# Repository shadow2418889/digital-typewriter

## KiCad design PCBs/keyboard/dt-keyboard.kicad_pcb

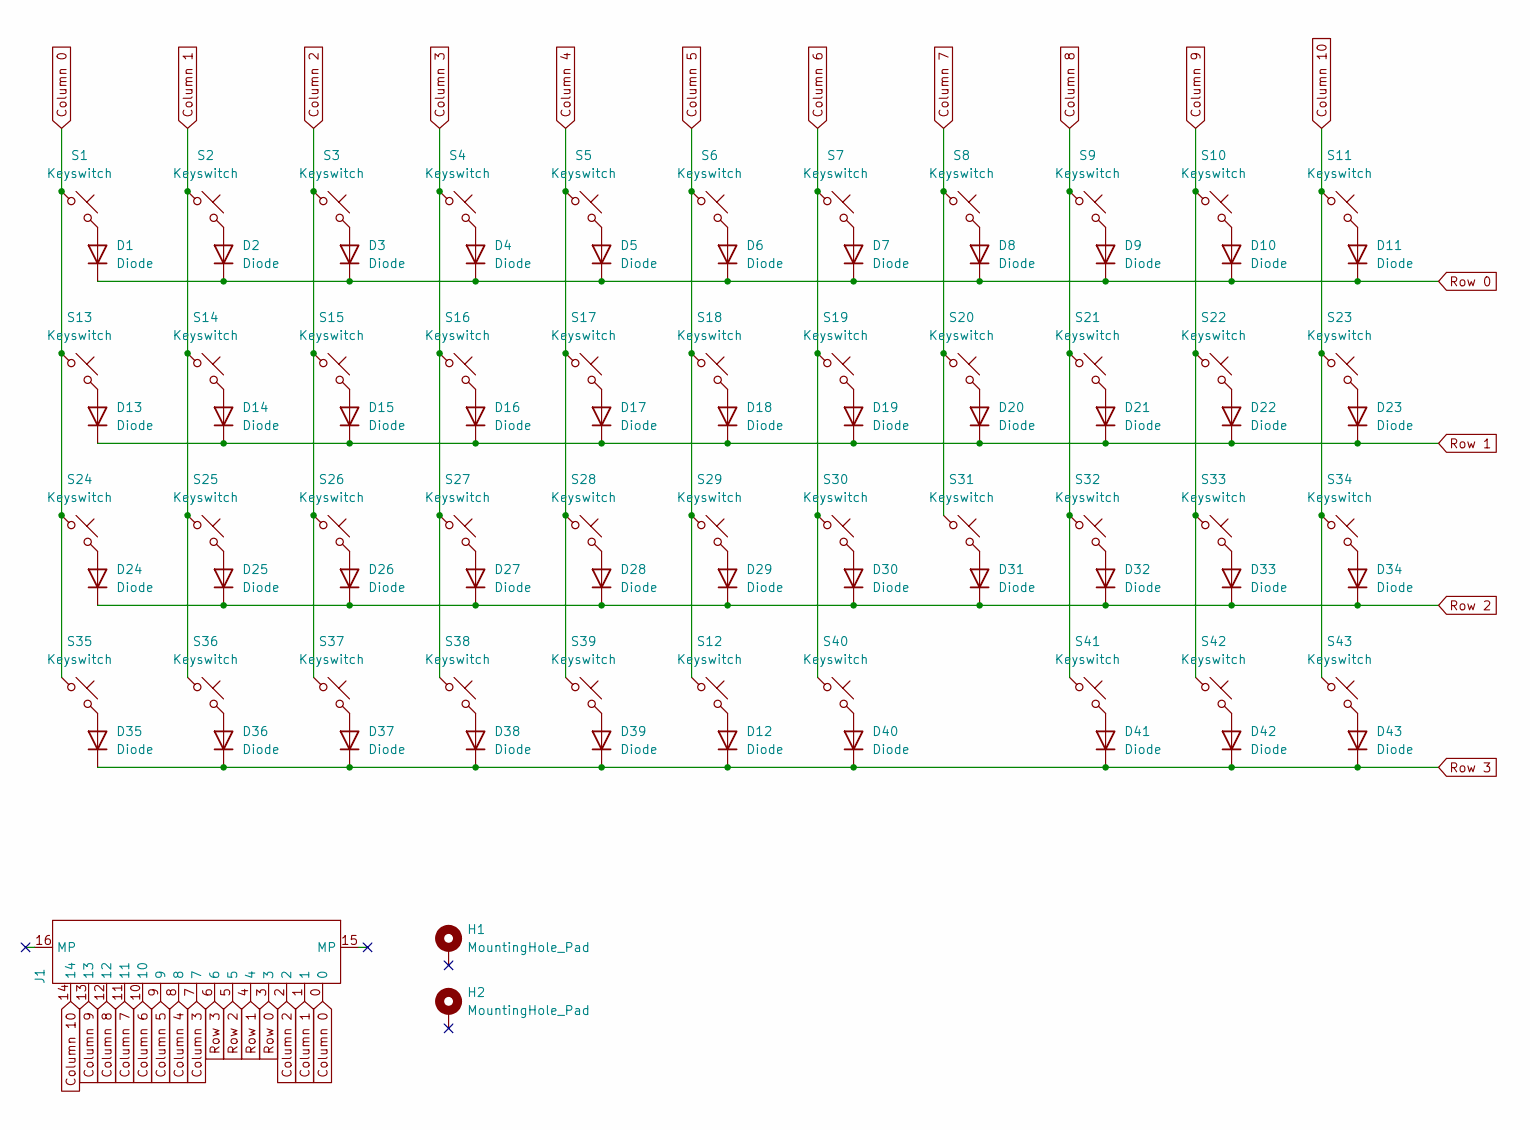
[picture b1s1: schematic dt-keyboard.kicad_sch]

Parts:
D1, D2, D3, D4, D5, D6, D7, D8, D9, D10, D11, D12, D13, D14, D15, D16, D17, D18, D19, D20, D21, D22, D23, D24, D25, D26, D27, D28, D29, D30, D31, D32, D33, D34, D35, D36, D37, D38, D39, D40, D41, D42, D43: Diode; Diode_SOD-123
H1, H2: MountingHole_Pad; MountingHole_3.2mm_M3_Pad_TopBottom
J1: FPC_15
S1, S2, S3, S4, S5, S6, S7, S8, S9, S10, S11, S12, S14, S15, S16, S17, S18, S19, S20, S21, S22, S25, S26, S27, S28, S29, S30, S31, S32, S34, S36, S37, S39, S41, S42: Keyswitch; MX Hotswap_Choc_V1_Plated_1.00u
S13, S33, S35, S43: Keyswitch; MX Hotswap_Choc_V1_Plated_1.25u
S23, S24: Keyswitch; MX Hotswap_Choc_V1_Plated_1.75u
S38, S40: Keyswitch; MX Hotswap_Choc_V1_Plated_2.25u

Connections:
Column 0: J1.0, S1.1, S13.1, S24.1, S35.1
Column 1: J1.1, S2.1, S14.1, S25.1, S36.1
Column 2: J1.2, S3.1, S15.1, S26.1, S37.1
Column 3: J1.7, S4.1, S16.1, S27.1, S38.1
Column 4: J1.8, S5.1, S17.1, S28.1, S39.1
Column 5: J1.9, S6.1, S12.1, S18.1, S29.1
Column 6: J1.10, S7.1, S19.1, S30.1, S40.1
Column 7: J1.11, S8.1, S20.1, S31.1
Column 8: J1.12, S9.1, S21.1, S32.1, S41.1
Column 9: J1.13, S10.1, S22.1, S33.1, S42.1
Column 10: J1.14, S11.1, S23.1, S34.1, S43.1
unnamed: D1.2 (A), S1.2
unnamed: D2.2 (A), S2.2
unnamed: D3.2 (A), S3.2
unnamed: D4.2 (A), S4.2
unnamed: D5.2 (A), S5.2
unnamed: D6.2 (A), S6.2
unnamed: D7.2 (A), S7.2
unnamed: D8.2 (A), S8.2
unnamed: D9.2 (A), S9.2
unnamed: D10.2 (A), S10.2
unnamed: D11.2 (A), S11.2
unnamed: D12.2 (A), S12.2
unnamed: D13.2 (A), S13.2
unnamed: D14.2 (A), S14.2
unnamed: D15.2 (A), S15.2
unnamed: D16.2 (A), S16.2
unnamed: D17.2 (A), S17.2
unnamed: D18.2 (A), S18.2
unnamed: D19.2 (A), S19.2
unnamed: D20.2 (A), S20.2
unnamed: D21.2 (A), S21.2
unnamed: D22.2 (A), S22.2
unnamed: D23.2 (A), S23.2
unnamed: D24.2 (A), S24.2
unnamed: D25.2 (A), S25.2
unnamed: D26.2 (A), S26.2
unnamed: D27.2 (A), S27.2
unnamed: D28.2 (A), S28.2
unnamed: D29.2 (A), S29.2
unnamed: D30.2 (A), S30.2
unnamed: D31.2 (A), S31.2
unnamed: D32.2 (A), S32.2
unnamed: D33.2 (A), S33.2
unnamed: D34.2 (A), S34.2
unnamed: D35.2 (A), S35.2
unnamed: D36.2 (A), S36.2
unnamed: D37.2 (A), S37.2
unnamed: D38.2 (A), S38.2
unnamed: D39.2 (A), S39.2
unnamed: D40.2 (A), S40.2
unnamed: D41.2 (A), S41.2
unnamed: D42.2 (A), S42.2
unnamed: D43.2 (A), S43.2
Row 0: D1.1 (K), D2.1 (K), D3.1 (K), D4.1 (K), D5.1 (K), D6.1 (K), D7.1 (K), D8.1 (K), D9.1 (K), D10.1 (K), D11.1 (K), J1.3
Row 1: D13.1 (K), D14.1 (K), D15.1 (K), D16.1 (K), D17.1 (K), D18.1 (K), D19.1 (K), D20.1 (K), D21.1 (K), D22.1 (K), D23.1 (K), J1.4
Row 2: D24.1 (K), D25.1 (K), D26.1 (K), D27.1 (K), D28.1 (K), D29.1 (K), D30.1 (K), D31.1 (K), D32.1 (K), D33.1 (K), D34.1 (K), J1.5
Row 3: D12.1 (K), D35.1 (K), D36.1 (K), D37.1 (K), D38.1 (K), D39.1 (K), D40.1 (K), D41.1 (K), D42.1 (K), D43.1 (K), J1.6

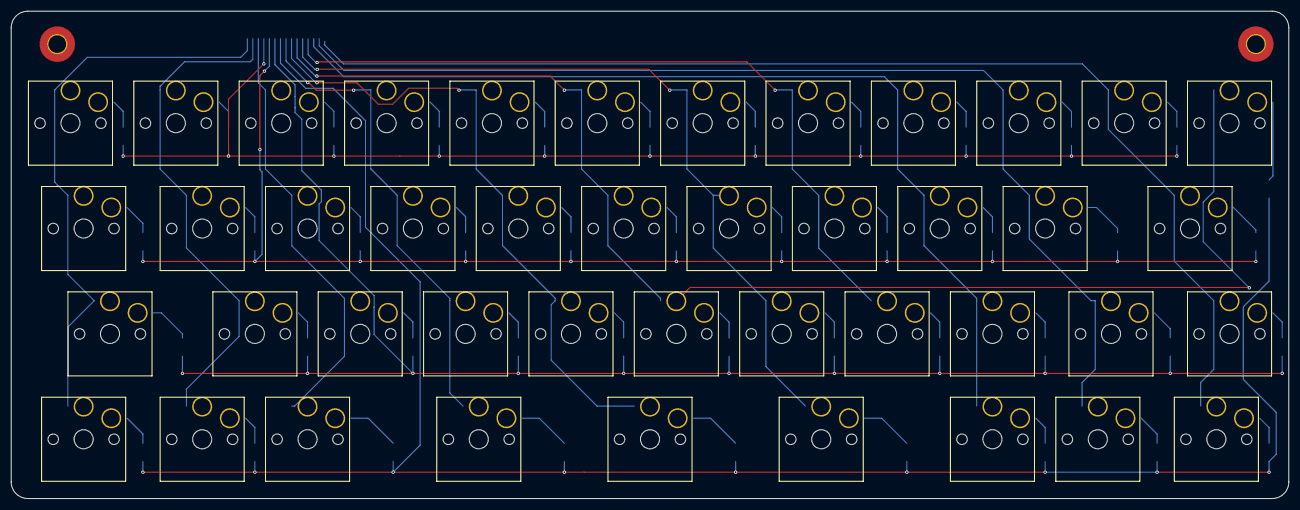
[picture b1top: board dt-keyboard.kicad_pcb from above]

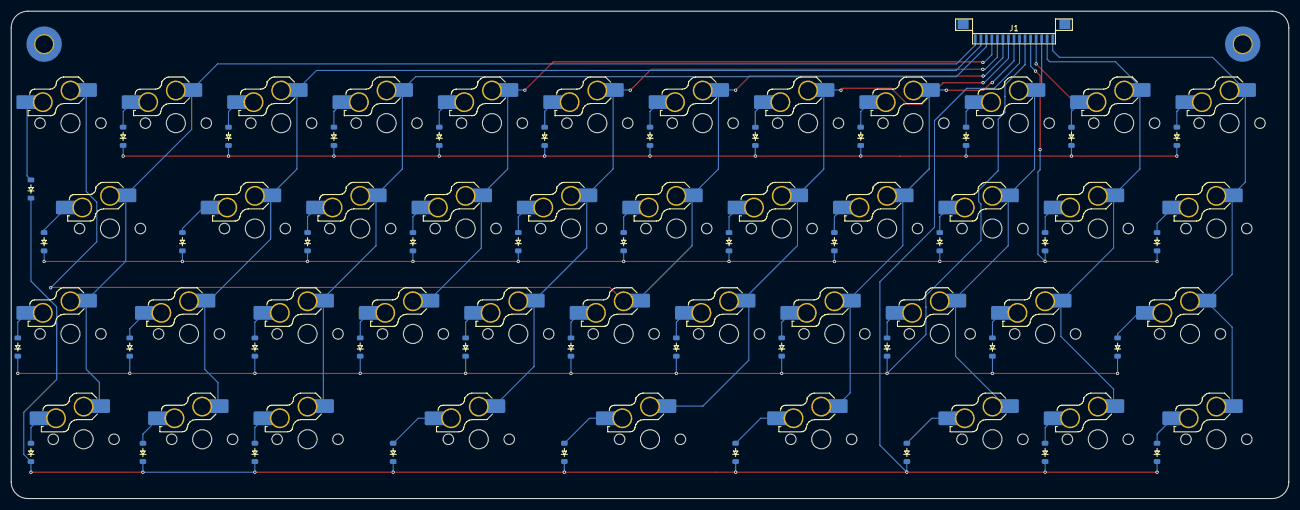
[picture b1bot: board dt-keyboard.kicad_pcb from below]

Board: 2 copper layers, 231.0 x 88.1 mm, 89 parts (44 on the bottom side), 58 nets.

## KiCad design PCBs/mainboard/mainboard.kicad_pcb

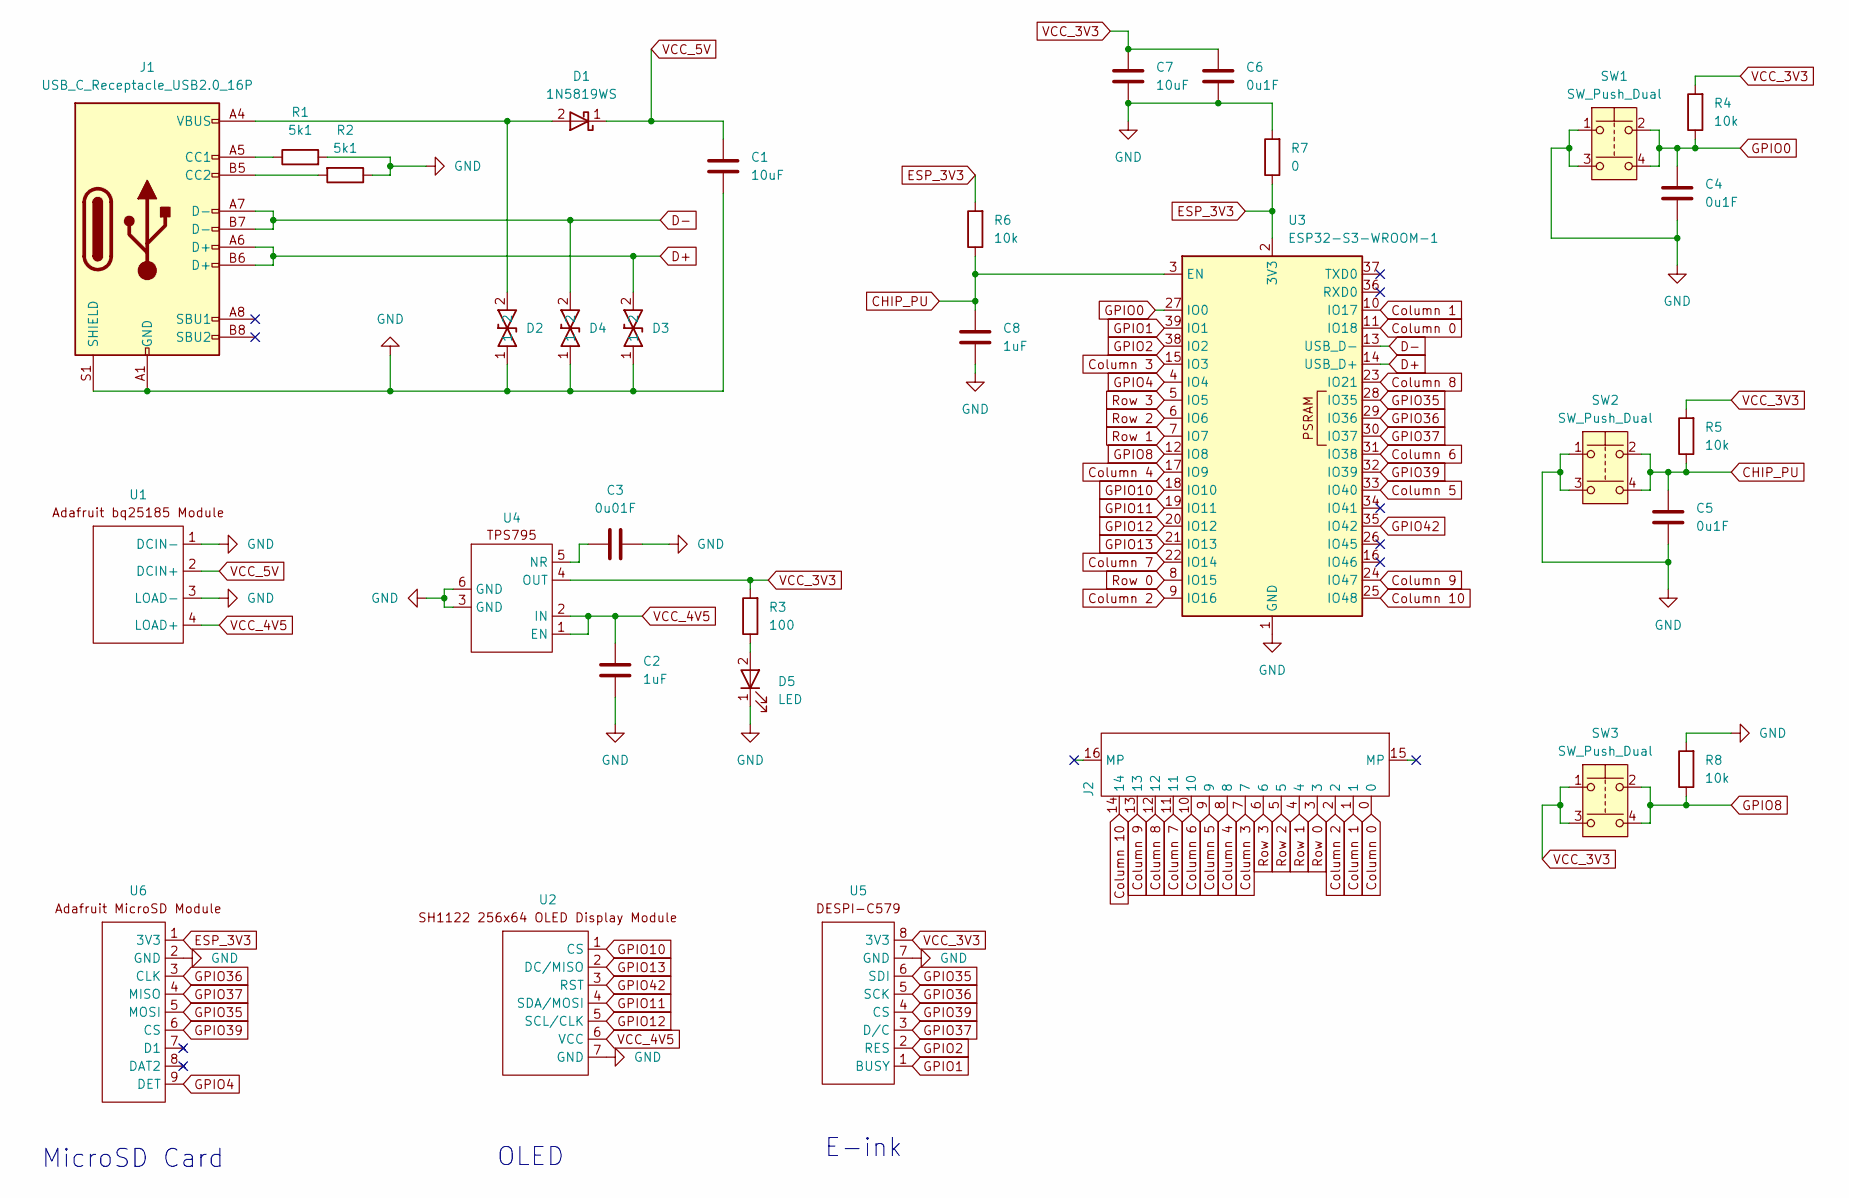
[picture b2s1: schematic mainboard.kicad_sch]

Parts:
C1, C7: 10uF; C_0805_2012Metric
C2, C8: 1uF; C_0805_2012Metric
C3: 0u01F; C_0805_2012Metric
C4, C5, C6: 0u1F; C_0805_2012Metric
D1: 1N5819WS; 1N5819HW-7-F
D2, D3, D4: LESD5D5
D5: LED; KT-0805G
J1: USB_C_Receptacle_USB2.0_16P; USB_C_Receptacle_16P
J2: FPC_15
R1, R2: 5k1; R_0805_2012Metric
R3: 100; R_0805_2012Metric
R4, R5, R6, R8: 10k; R_0805_2012Metric
R7: 0; R_0805_2012Metric
SW1, SW2, SW3: SW_Push_Dual; B3F-1000
U1: Adafruit bq25185 Module
U2: SH1122 256x64 OLED Display Module
U3: ESP32-S3-WROOM-1
U4: TPS795
U5: DESPI-C579
U6: Adafruit MicroSD Module

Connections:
CHIP_PU: C5.1, C8.1, R5.1, R6.1, SW2.2, SW2.4, U3.3 (EN)
Column 0: J2.0, U3.11 (IO18)
Column 1: J2.1, U3.10 (IO17)
Column 2: J2.2, U3.9 (IO16)
Column 3: J2.7, U3.15 (IO3)
Column 4: J2.8, U3.17 (IO9)
Column 5: J2.9, U3.33 (IO40)
Column 6: J2.10, U3.31 (IO38)
Column 7: J2.11, U3.22 (IO14)
Column 8: J2.12, U3.23 (IO21)
Column 9: J2.13, U3.24 (IO47)
Column 10: J2.14, U3.25 (IO48)
D+: D3.2, J1.A6 (D+), J1.B6 (D+), U3.14 (USB_D+)
D-: D4.2, J1.A7 (D-), J1.B7 (D-), U3.13 (USB_D-)
ESP_3V3: R6.2, R7.1, U3.2 (3V3), U6.1 (3V3)
GND: C1.2, C2.2, C3.1, C4.2, C5.2, C6.2, C7.2, C8.2, D2.1, D3.1, D4.1, D5.1 (K), J1.A1 (GND), J1.A12 (GND), J1.B1 (GND), J1.B12 (GND), J1.S1 (SHIELD), R1.2, R2.1, R7.2, R8.2, SW1.1, SW1.3, SW2.1, SW2.3, U1.1 (DCIN-), U1.3 (LOAD-), U2.7 (GND), U3.1 (GND), U3.40 (GND), U3.41 (GND), U4.3 (GND), U4.6 (GND), U5.7 (GND), U6.2 (GND)
GPIO0: C4.1, R4.1, SW1.2, SW1.4, U3.27 (IO0)
GPIO1: U3.39 (IO1), U5.1 (BUSY)
GPIO2: U3.38 (IO2), U5.2 (RES)
GPIO4: U3.4 (IO4), U6.9 (DET)
GPIO8: R8.1, SW3.2, SW3.4, U3.12 (IO8)
GPIO10: U2.1 (CS), U3.18 (IO10)
GPIO11: U2.4 (SDA/MOSI), U3.19 (IO11)
GPIO12: U2.5 (SCL/CLK), U3.20 (IO12)
GPIO13: U2.2 (DC/MISO), U3.21 (IO13)
GPIO35: U3.28 (IO35), U5.6 (SDI), U6.5 (MOSI)
GPIO36: U3.29 (IO36), U5.5 (SCK), U6.3 (CLK)
GPIO37: U3.30 (IO37), U5.3 (D/C), U6.4 (MISO)
GPIO39: U3.32 (IO39), U5.4 (CS), U6.6 (CS)
GPIO42: U2.3 (RST), U3.35 (IO42)
unnamed: D1.2 (A), D2.2, J1.A4 (VBUS), J1.A9 (VBUS), J1.B4 (VBUS), J1.B9 (VBUS)
unnamed: D5.2 (A), R3.1
unnamed: J1.A5 (CC1), R1.1
unnamed: J1.B5 (CC2), R2.2
unnamed: C3.2, U4.5 (NR)
Row 0: J2.3, U3.8 (IO15)
Row 1: J2.4, U3.7 (IO7)
Row 2: J2.5, U3.6 (IO6)
Row 3: J2.6, U3.5 (IO5)
VCC_3V3: C6.1, C7.1, R3.2, R4.2, R5.2, SW3.1, SW3.3, U4.4 (OUT), U5.8 (3V3)
VCC_4V5: C2.1, U1.4 (LOAD+), U2.6 (VCC), U4.1 (EN), U4.2 (IN)
VCC_5V: C1.1, D1.1 (K), U1.2 (DCIN+)

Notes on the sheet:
MicroSD Card
OLED
E-ink

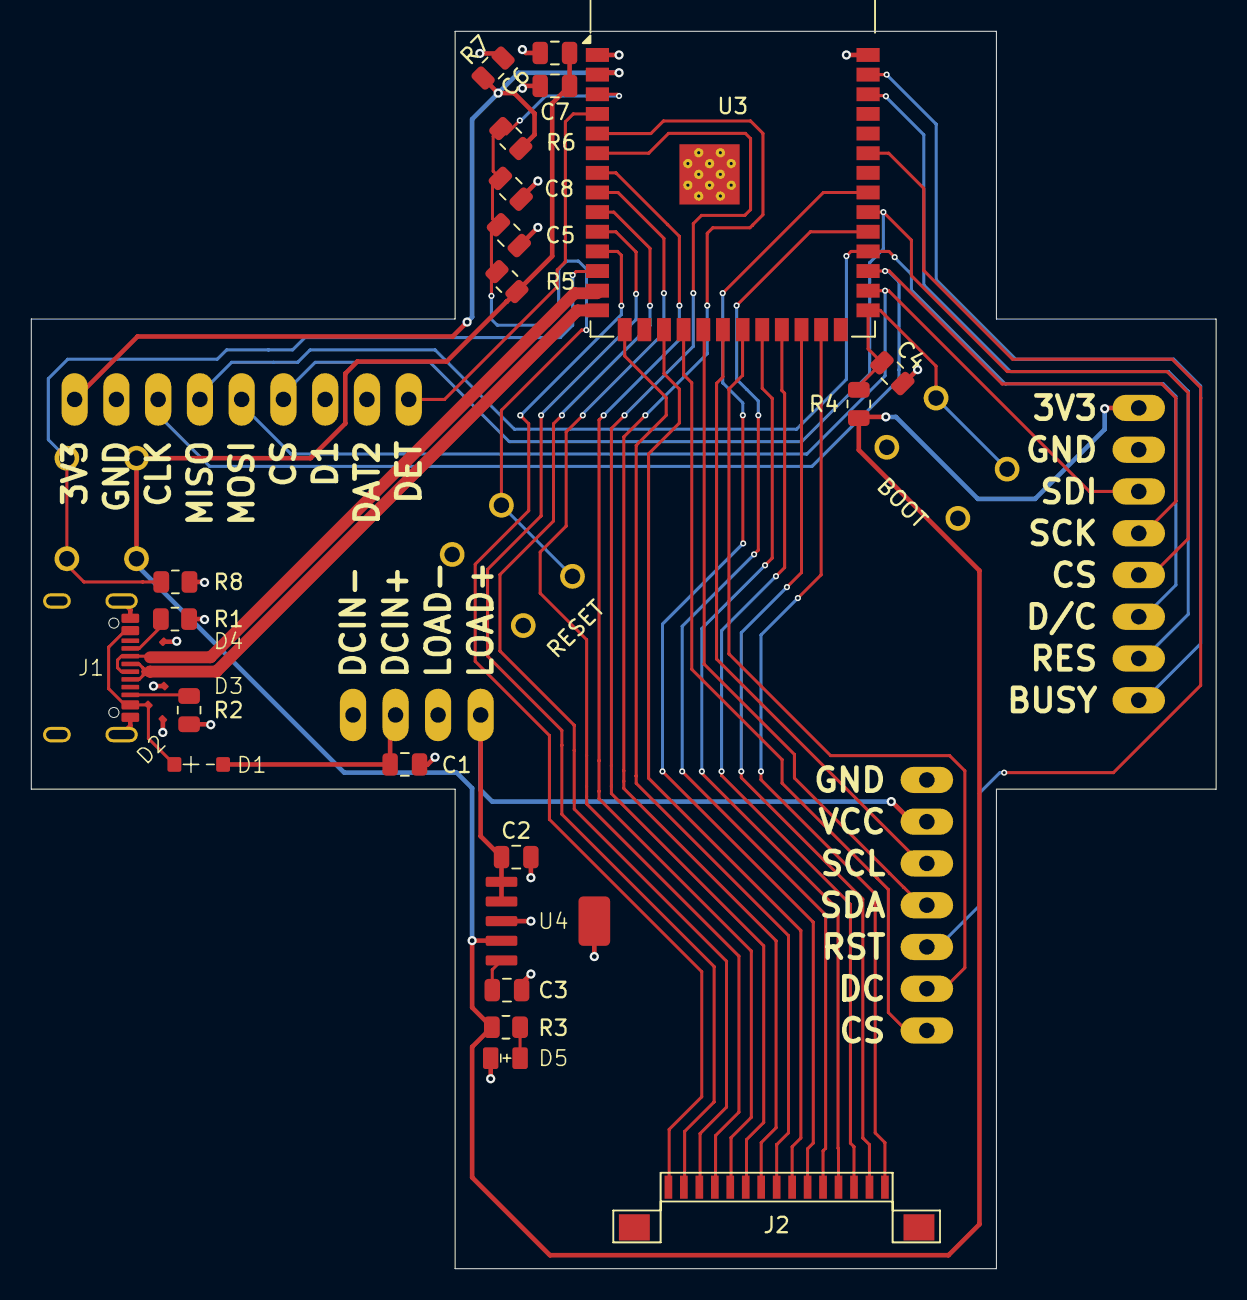
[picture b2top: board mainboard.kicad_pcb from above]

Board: 4 copper layers, 76.6 x 80.0 mm, 32 parts (0 on the bottom side), 42 nets.

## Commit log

2025-07-16 Started work on PCB
2025-07-18 Finished Keyboard PCB
2025-07-19 Fixed Keyboard
2025-07-20 Worked on power system
2025-07-21 Added ESP32 to Schematic
2025-07-23 Tested OLED
2025-07-30 Fixed Display Code + Added Peripherals on Schematic
2025-07-30 CAD Mockup and Footprint Design
2025-08-01 Layouting + Deep Sleep Tests
2025-08-02 Layouting pt.1
2025-08-14 Routed peripherals
2025-12-10 Verification
